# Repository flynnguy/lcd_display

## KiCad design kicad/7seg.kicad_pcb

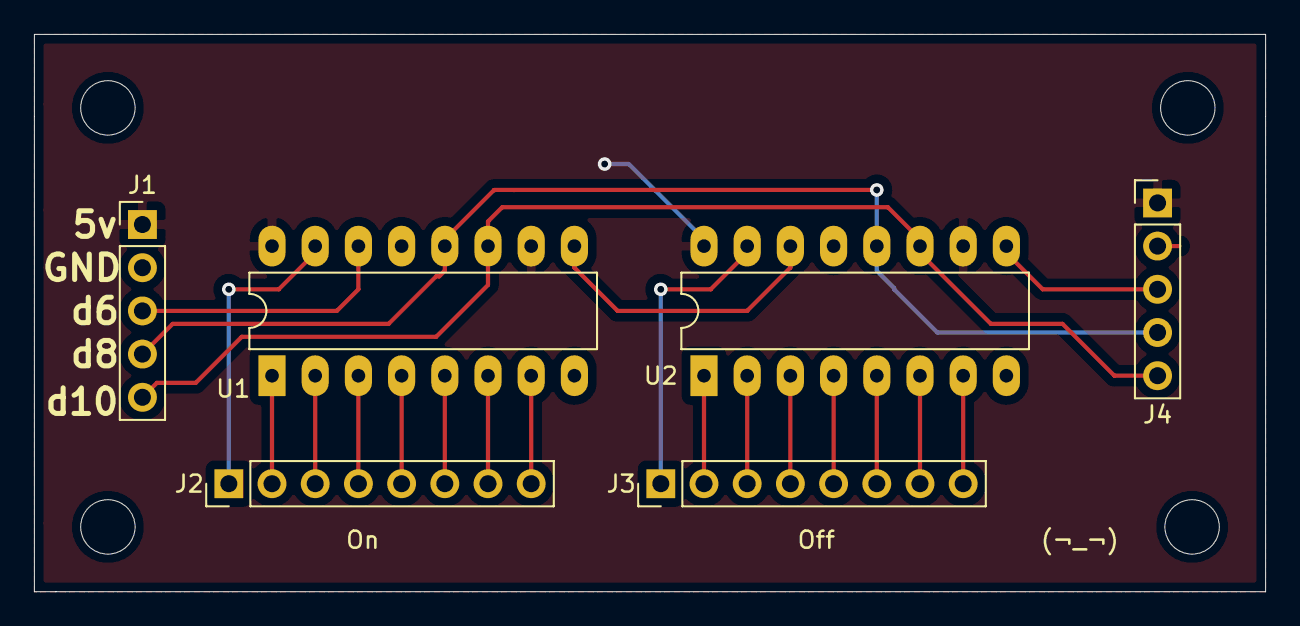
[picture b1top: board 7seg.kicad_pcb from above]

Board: 2 copper layers, 72.4 x 32.8 mm, 6 parts (0 on the bottom side), 23 nets.

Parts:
J1, J4: Conn_01x05; PinHeader_1x05_P2.54mm_Vertical
J2, J3: Conn_01x08; PinHeader_1x08_P2.54mm_Vertical
U1, U2: 74HC595; DIP-16_W7.62mm_LongPads

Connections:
+5V: J1.1, J4.1, U1.10, U1.16, U2.10, U2.16
/d6: J1.3, U1.14
/d8: J1.4, J4.4, U1.12, U2.12
/d10: J1.5, J4.5, U1.11, U2.11
GND: J1.2, J4.2, U1.8, U1.13, U2.8, U2.13
unnamed: J2.1, U1.15
unnamed: J2.2, U1.1
unnamed: J2.3, U1.2
unnamed: J2.4, U1.3
unnamed: J2.5, U1.4
unnamed: J2.6, U1.5
unnamed: J2.7, U1.6
unnamed: J2.8, U1.7
unnamed: J3.1, U2.15
unnamed: J3.2, U2.1
unnamed: J3.3, U2.2
unnamed: J3.4, U2.3
unnamed: J3.5, U2.4
unnamed: J3.6, U2.5
unnamed: J3.7, U2.6
unnamed: J3.8, U2.7
unnamed: J4.3, U2.9
unnamed: U1.9, U2.14

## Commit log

2023-02-26 Added kicad files
